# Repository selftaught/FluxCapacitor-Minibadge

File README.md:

# SaintCon 2022 - Flux Capacitor Minibadge

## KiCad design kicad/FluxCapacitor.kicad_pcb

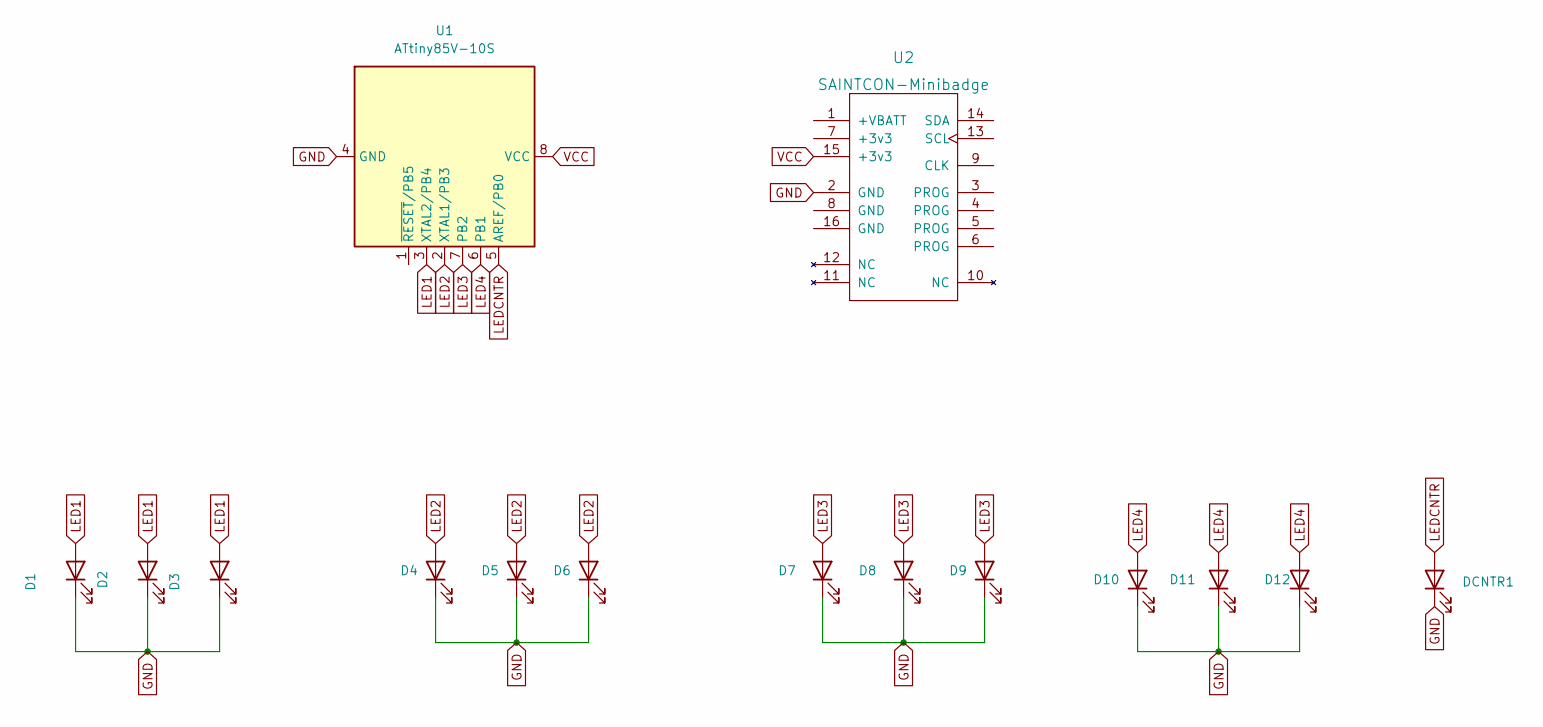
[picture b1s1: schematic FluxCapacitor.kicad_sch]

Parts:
D1, D2, D3, D4, D5, D6, D7, D8, D9, D10, D11, D12: LED; LED_0402_1005Metric_Pad0.77x0.64mm_HandSolder
DCNTR1: LED; LED_0402_1005Metric_Pad0.77x0.64mm_HandSolder
U1: ATtiny85V-10S; SOIC-8W_5.3x5.3mm_P1.27mm
U2: SAINTCON-Minibadge; SAINTCON-Simple

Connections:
GND: D1.1 (K), D2.1 (K), D3.1 (K), D4.1 (K), D5.1 (K), D6.1 (K), D7.1 (K), D8.1 (K), D9.1 (K), D10.1 (K), D11.1 (K), D12.1 (K), DCNTR1.1 (K), U1.4 (GND), U2.2 (GND)
LED1: D1.2 (A), D2.2 (A), D3.2 (A), U1.3 (XTAL2/PB4)
LED2: D4.2 (A), D5.2 (A), D6.2 (A), U1.2 (XTAL1/PB3)
LED3: D7.2 (A), D8.2 (A), D9.2 (A), U1.7 (PB2)
LED4: D10.2 (A), D11.2 (A), D12.2 (A), U1.6 (PB1)
LEDCNTR: DCNTR1.2 (A), U1.5 (AREF/PB0)
unnamed: U1.8 (VCC), U2.15 (+3v3)

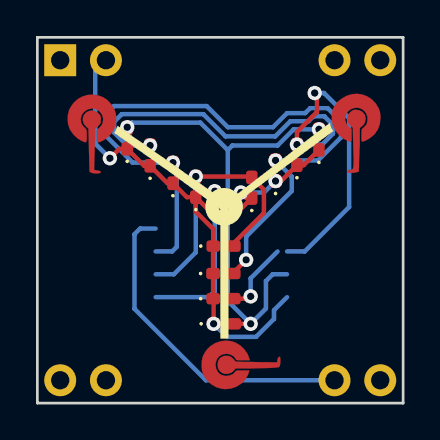
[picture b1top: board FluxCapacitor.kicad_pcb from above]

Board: 2 copper layers, 20.3 x 20.3 mm, 16 parts (1 on the bottom side), 7 nets.

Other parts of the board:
Ref**: Val**; fluxcapacitor

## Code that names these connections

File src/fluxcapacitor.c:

/**
 * Project: SaintCon Flux Capacitor Minibadge
 * Author: Dillan Hildebrand
 * Date: 09/21/2022
 */
#include <avr/io.h>
#include "Arduino.h"

/* Breadboard pins
#define LED_SEG_1_PIN PB1
#define LED_SEG_2_PIN PB2
#define LED_SEG_3_PIN PB0
#define LED_SEG_4_PIN PB4
#define LED_SEG_0_PIN PB3 // center led
*/

// Minibadge Pins
#define LED_SEG_0_PIN PB0 // center led
#define LED_SEG_1_PIN PB4
#define LED_SEG_2_PIN PB3
#define LED_SEG_3_PIN PB2
#define LED_SEG_4_PIN PB1

const int NUM_LEDS = 5;

int leds[5] = {
    LED_SEG_1_PIN,
    LED_SEG_2_PIN,
    LED_SEG_3_PIN,
    LED_SEG_4_PIN,
    LED_SEG_0_PIN};


void setup()
{
    for (int i = 0; i < NUM_LEDS; i++)
    {
        pinMode(leds[i], OUTPUT);
    }
}

void loop()
{
    for (int i = 0; i < 30; i++)
    {
        int d = (i <= 25 ? 40 - i : 20);
        for (int i = 0; i < NUM_LEDS; i++)
        {
            PORTB |= (1 << leds[i]); // led on
            delay(d);
            PORTB &= ~(1 << leds[i]); // led off
        }
        delay(100);
    }
    delay(3000);
}

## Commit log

2023-12-30 first
2023-12-30 remove images from readme for now
